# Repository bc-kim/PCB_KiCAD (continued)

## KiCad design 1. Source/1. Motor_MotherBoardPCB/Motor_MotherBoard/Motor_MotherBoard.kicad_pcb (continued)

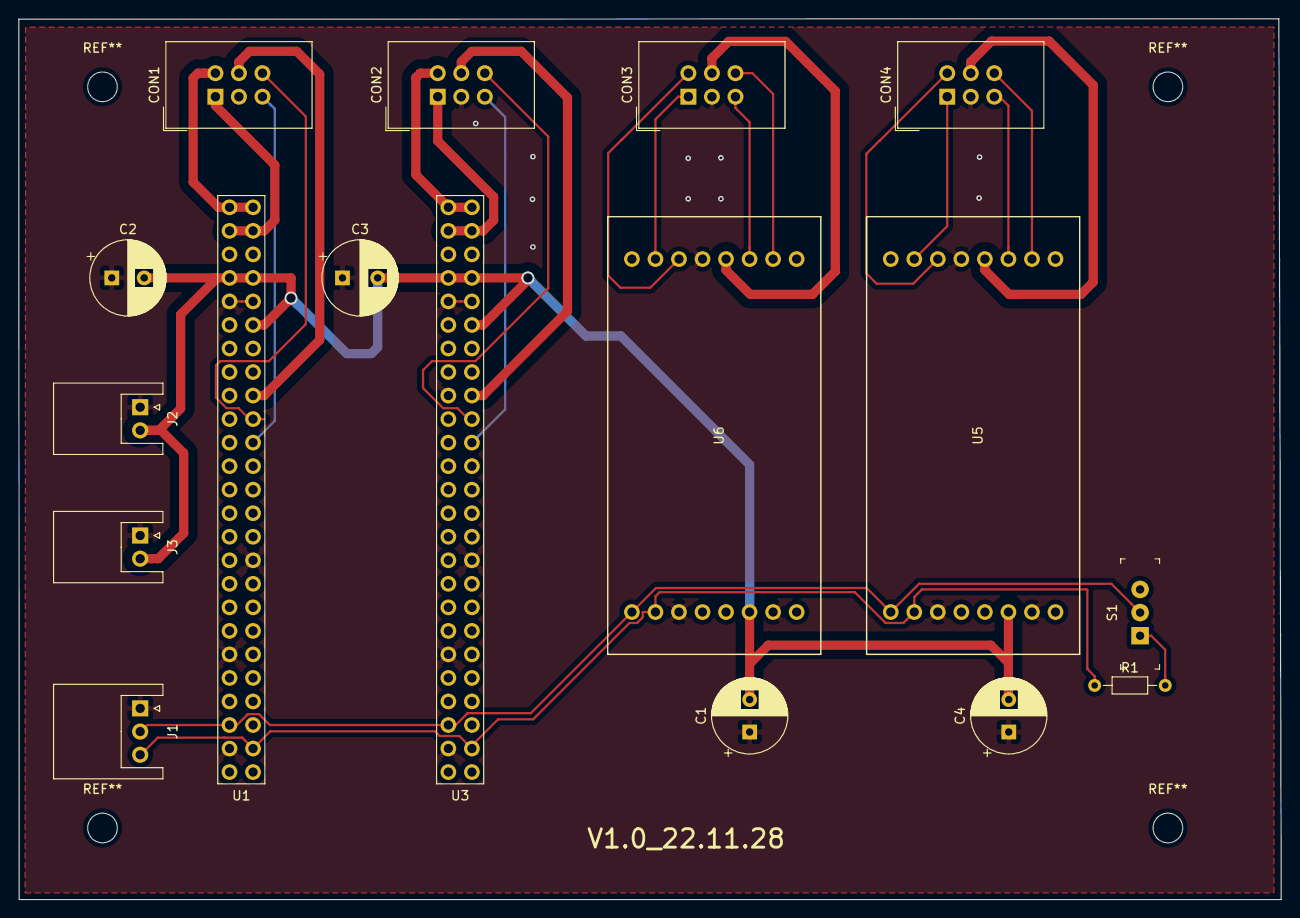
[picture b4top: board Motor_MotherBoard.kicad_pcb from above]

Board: 2 copper layers, 136.3 x 95.1 mm, 17 parts (0 on the bottom side), 25 nets.

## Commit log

2022-10-31 1st Commit
2022-10-31 Libraries 추가
2022-11-01 FileAdjust
2022-11-21 Made-code workspace
2022-11-21 Loadcell.pro_commit
2022-11-27 PCB_MotorMotherBoard
    PCB_MotorMotherBoard
2022-11-28 MotorMotherBoard설계완료
2022-11-29 MCU_MotherBoard
    MCU_MotherBoard
2022-11-29 Add LoadCell_Click4 and SDCARD libraries
    Add LoadCell_Click4 and SDCARD libraries
2022-11-29 Schematic finished
    - change cap`s footprint to smd type
    - artwork should be done.
2022-11-30 MCUBoard작업
2022-11-30 MCU_MotherBoard마무리
2022-12-06 Include GBR files and log.md file
2022-12-08 Upgrade to KiCAD6.0
